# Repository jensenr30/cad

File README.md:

# Ryan's CAD Files (Schematics, PCBs, Simulations)

## kicad5
I started using KiCad 5.1.2 to draw schematics and lay out PCBs in May 2019.

## kicad4
I used KiCad 4.0.6 for 3 weeks in September 2017. The two projects I completed are:
* [Shift-Register Break-Out-Board](/kicad4/SRBOB) - A modular daisy-chain-able serial-in-parallel-out 74hc595-based shift register circuit board.
* [XPhone Input Board](/kicad4/XPhone/Input_Board) - A quad transducer amplifier and glockenspiel-key-hit-detection circuit board.

## eagle6
Eagle was the first CAD program I ever used. I started using Eagle (on version 5.11.0) sometime in early 2011. I stopped on version 6.6.0 in mid 2017.  Some of the more interesting projects I completed using Eagle are:
* [Analog Synth](eagle6/Analog%20Synth) - a bunch of analog (and digital) DIY synth modules.  Designed, built, and tested by your truly.  This includes VCOs, VCFs, VCAs, sequencers, front-panel designs, digital delay, manual oscillators, and power-distribution interconnect PCBs.
* [Stroboscope](eagle6/Stroboscope) - a device that can turn on and off LEDs very fast (at audio frequencies) in order to produce interesting/useful/helpful visual effects.  A stroboscope can be used to enable a human to monitor the rotation of things in real time, e.g. fans, drills, wheels, motors, spinning objects, guitar strings, and any other object engaged in cyclic motion.
* [VU Meter](eagle6/VU%20meter) - a circuit that represents audio amplitude vertically on several bargraphs (each bargraph displays the amplitude of a given section of the audio spectrum).  The device can be used to build a real-time visual audio spectrum analyzer.
* [FreqCount84](eagle6/FreqCount84) - Atmel microcontroller-based design for precise measurement of frequency of square waves.  I believe the hwardware & firmware achieved an accuracy of ± a few ppm with the help of a 1.5 pm TCXO.
* [9x9 LED Matrix](eagle6/9x9%20LED%20Matrix) - a 2D array of LEDs (9 LEDs wide, 9 LEDs tall).  I remember wanting to build an array that had an odd number of pixels because it would allow me to make symetric visual displays.  I programmed a game of pong for this 9x9 LED Matrix.  That code exists in [my repo for Arduino programs](https://github.com/jensenr30/Arduino/tree/master/_DISPLAY/9x9_LED_Matrix).
* [Prototype Boards](eagle6/Prototype%20Boards) - three PCBs that enable DIY circuit construction.  0.1"-arrays of SMD pads, 0.1"-arrays of through-holes, SOT-to-DIP break-out-boards, SOIC-to-DIP break-out-boards, etc...

## LTspice IV
I have used [LTspice](https://en.wikipedia.org/wiki/LTspice) version IV to simulate some of my circuits.

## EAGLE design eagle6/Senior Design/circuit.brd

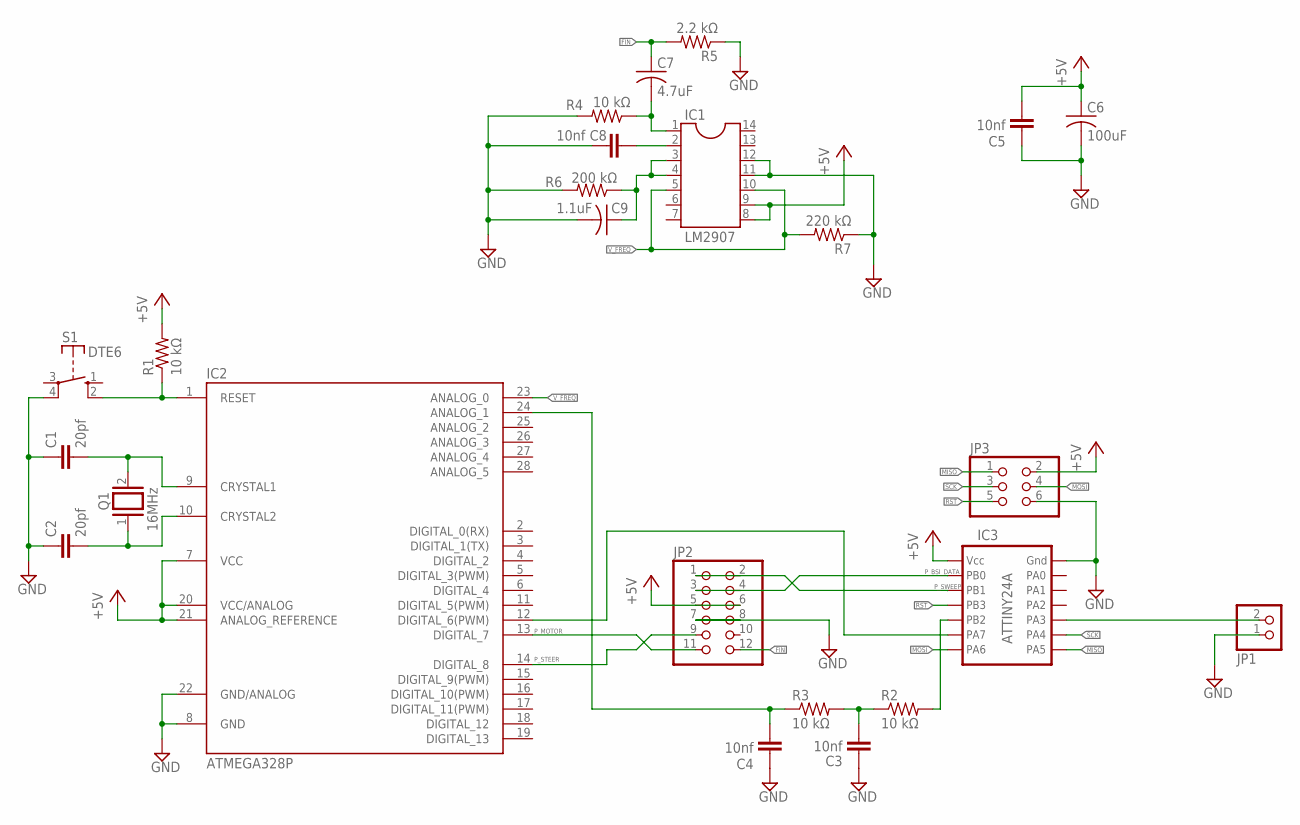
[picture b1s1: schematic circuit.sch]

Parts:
C1, C2: 20pf; C025-024X044
C3, C4, C5, C8: 10nf; C025-024X044
C6: 100uF; C025-050X050
C7: 4.7uF; C025-050X050
C9: 1.1uF; C025-050X050
IC1: LM2907; DIL14
IC2: ATMEGA328P; DIL28-3
IC3: ATTINY24A; TINY24A
JP1: PINHD-1X2; 1X02
JP2: PINHD-2X6; 2X06
JP3: PINHD-2X3; 2X03
Q1: 16MHz; QS
R1, R2, R3, R4: 10 kΩ; 0204V
R5: 2.2 kΩ; 0204V
R6: 200 kΩ; 0204V
R7: 220 kΩ; 0204V
S1: DTE6

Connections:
+5V: C5.2, C6.1, IC1.8, IC1.9, IC2.7 (VCC), IC2.20 (VCC/ANALOG), IC2.21 (ANALOG_REFERENCE), IC3.1, JP2.5, JP2.6, JP3.2, R1.2
DATA-READY: IC2.12 (DIGITAL_6(PWM)), IC3.6
FIN: C7.1, JP2.12, R5.2
GND: C1.1, C2.1, C3.1, C4.1, C5.1, C6.2, C8.1, C9.2, IC1.11, IC1.12, IC2.8 (GND), IC2.22 (GND/ANALOG), IC3.14, JP1.1, JP2.7, JP2.8, JP3.6, R4.2, R5.1, R6.2, R7.1, S1.4
LINE-POSITION: C4.2, IC2.24 (ANALOG_1), R3.1
MISO: IC3.8, JP3.1
MOSI: IC3.7, JP3.4
unnamed: C9.1, IC1.3, IC1.4, R6.1
unnamed: IC3.10, JP1.2
unnamed: IC3.5, R2.2
unnamed: C1.2, IC2.9 (CRYSTAL1), Q1.2
unnamed: C2.2, IC2.10 (CRYSTAL2), Q1.1
unnamed: C3.2, R2.1, R3.2
unnamed: IC2.1 (RESET), R1.1, S1.2 (S)
unnamed: C7.2, IC1.1, R4.1
unnamed: C8.2, IC1.2
P_BSI_DATA: IC3.2, JP2.3, JP2.4
P_MOTOR: IC2.13 (DIGITAL_7), JP2.11
P_STEER: IC2.14 (DIGITAL_8), JP2.9
P_SWEEP: IC3.3, JP2.1, JP2.2
RST: IC3.4, JP3.5
SCK: IC3.9, JP3.3
V_FREQ: IC1.5, IC1.10, IC2.23 (ANALOG_0), R7.2

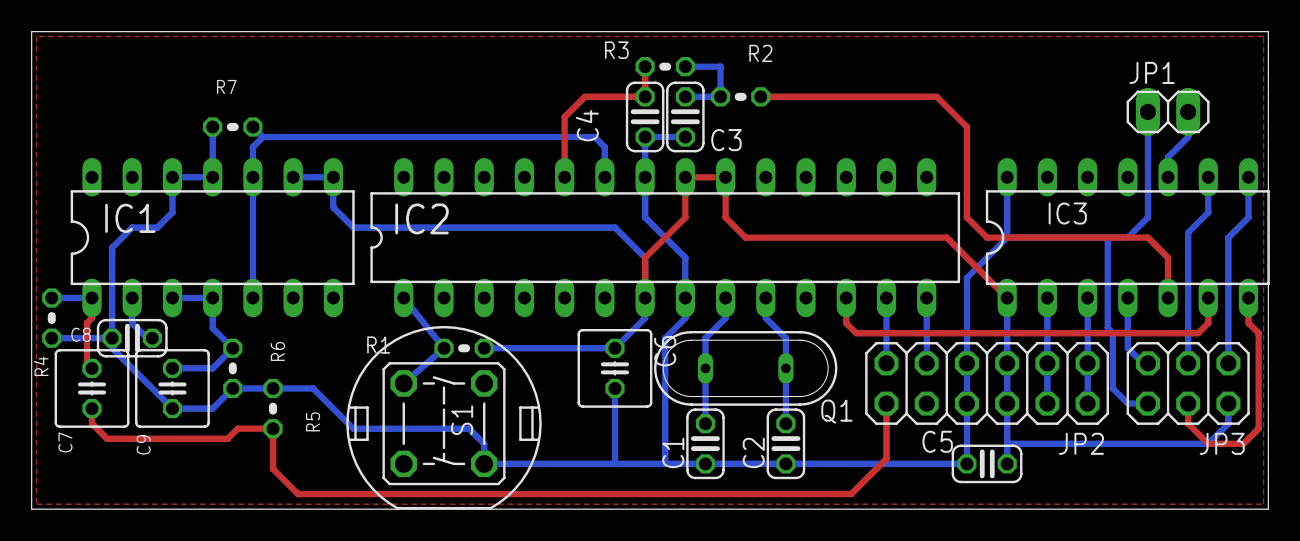
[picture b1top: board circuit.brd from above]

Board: 2 copper layers, 78.1 x 30.1 mm, 24 parts (0 on the bottom side), 23 nets.

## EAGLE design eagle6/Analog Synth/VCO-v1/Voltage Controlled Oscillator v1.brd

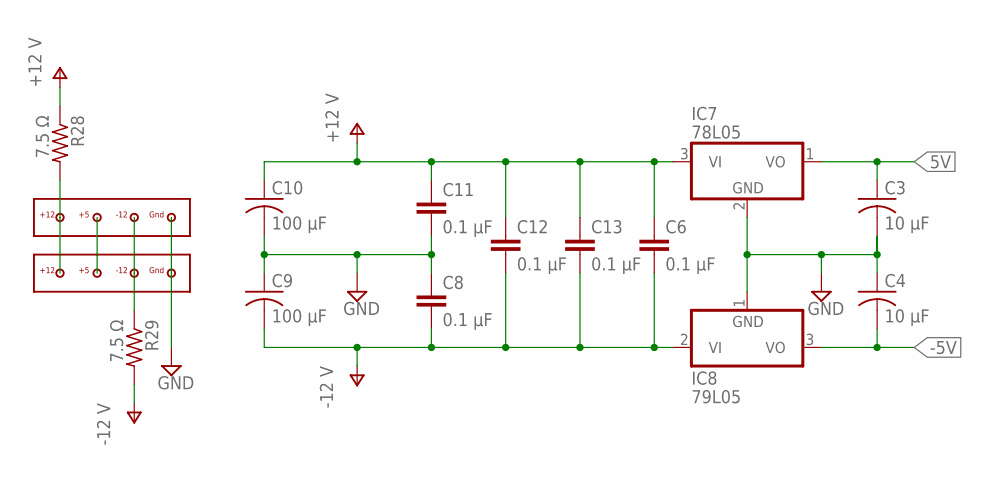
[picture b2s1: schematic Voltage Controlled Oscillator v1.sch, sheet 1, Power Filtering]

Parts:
C3, C4: 10 µF; C025-060X050
C6, C8, C11, C12, C13: 0.1 µF; C5B2.5
C9, C10: 100 µF; C025-060X050
IC7: 78L05; TO92
IC8: 79L05; TO92
R28, R29: 7.5 Ω; 0204/7
U$1, U$2: POWER_CONNECTOR_4_RGBB

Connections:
5V: C3.1, IC7.1 (VO); also elsewhere on the board
-5V: C4.2, IC8.3 (VO); also elsewhere on the board
GND: C3.2, C4.1, C8.1, C9.1, C10.2, C11.2, IC7.2 (GND), IC8.1 (GND), U$1.GND, U$2.GND; also elsewhere on the board
unnamed: U$1.+5, U$2.+5
unnamed: R28.2, U$1.+12, U$2.+12
unnamed: R29.1, U$1.-12, U$2.-12
V+: C6.1, C10.1, C11.1, C12.1, C13.1, IC7.3 (VI), R28.1; also elsewhere on the board
V-: C6.2, C8.2, C9.2, C12.2, C13.2, IC8.2 (VI), R29.2; also elsewhere on the board

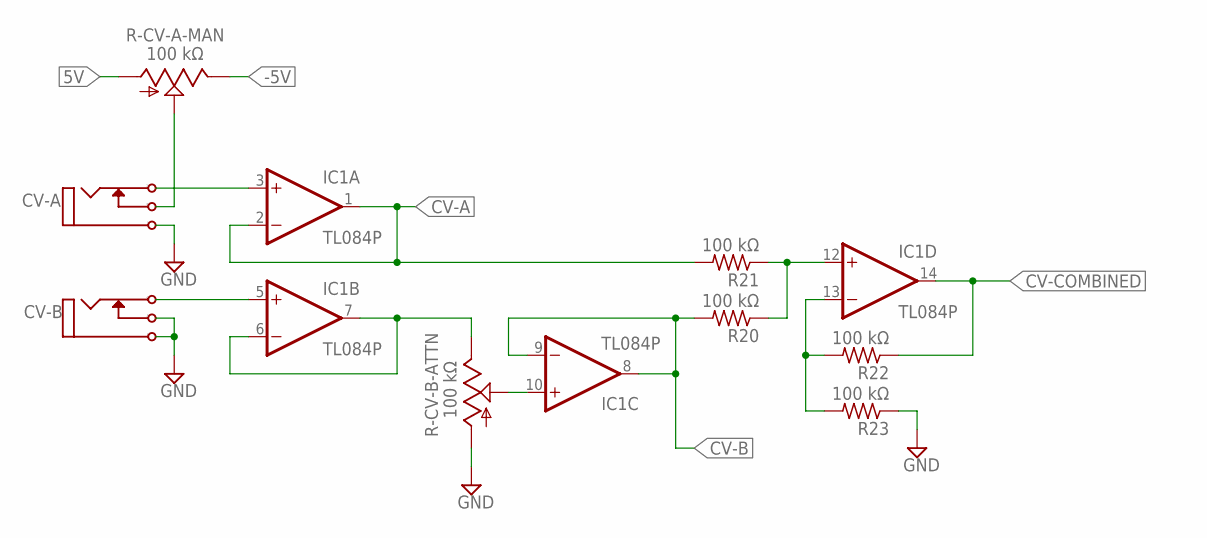
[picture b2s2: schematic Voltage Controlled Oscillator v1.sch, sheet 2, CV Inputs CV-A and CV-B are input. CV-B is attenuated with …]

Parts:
CV-A: I/O; MONO_JACK
CV-B: I/O; MONO_JACK
IC1: TL084P; DIL14
R20, R21, R22, R23: 100 kΩ; 0204/7
R-CV-A-MAN: 100 kΩ; B64Y
R-CV-B-ATTN: 100 kΩ; B64Y

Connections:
5V: R-CV-A-MAN.A; also elsewhere on the board
-5V: R-CV-A-MAN.E; also elsewhere on the board
CV-A: IC1.1 (OUT), IC1.2 (-IN), R21.2; also elsewhere on the board
CV-B: IC1.8 (OUT), IC1.9 (-IN), R20.2; also elsewhere on the board
CV-COMBINED: IC1.14 (OUT), R22.1; also elsewhere on the board
GND: CV-A.P$1, CV-B.P$1, CV-B.P$3 (P3), R23.1, R-CV-B-ATTN.A; also elsewhere on the board
unnamed: IC1.10 (+IN), R-CV-B-ATTN.S
unnamed: CV-A.P$2 (P2), IC1.3 (+IN)
unnamed: CV-A.P$3 (P3), R-CV-A-MAN.S
unnamed: IC1.12 (+IN), R20.1, R21.1
unnamed: IC1.13 (-IN), R22.2, R23.2
unnamed: CV-B.P$2 (P2), IC1.5 (+IN)
unnamed: IC1.6 (-IN), IC1.7 (OUT), R-CV-B-ATTN.E
V+: IC1.4 (V+); also elsewhere on the board
V-: IC1.11 (V-); also elsewhere on the board

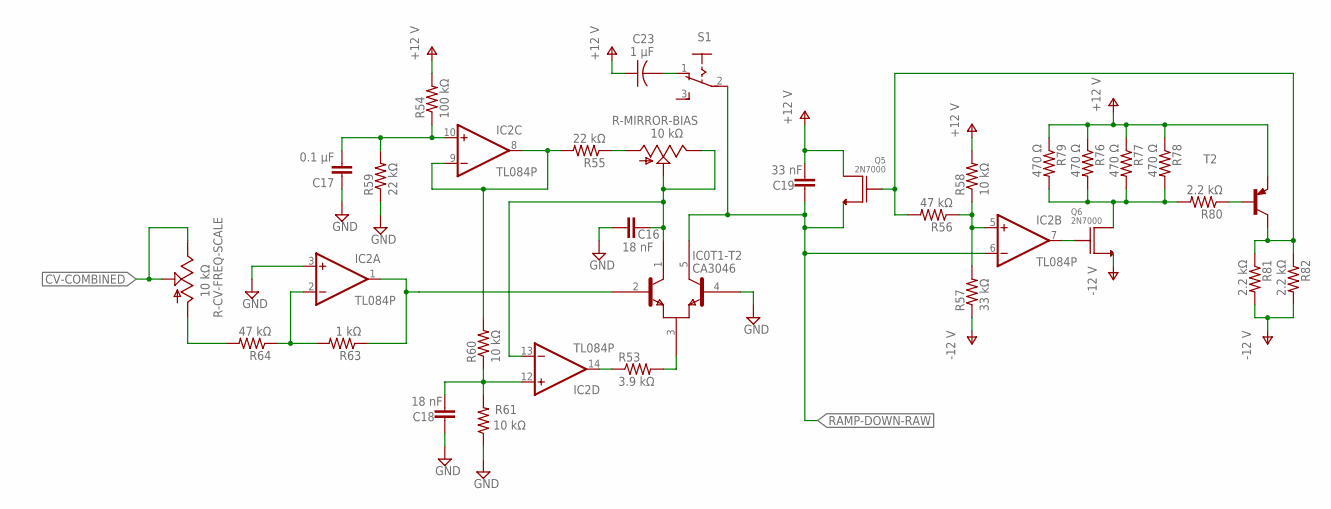
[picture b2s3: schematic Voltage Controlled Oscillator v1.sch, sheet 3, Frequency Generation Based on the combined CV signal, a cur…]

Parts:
C16, C18: 18 nF; C2.5-2
C17: 0.1 µF; C5B2.5
C19: 33 nF; C2.5-2
C23: 1 µF; C025-060X050
IC0: CA3046; DIL14
IC2: TL084P; DIL14
Q5, Q6: 2N7000
R53: 3.9 kΩ; 0204/7
R54: 100 kΩ; 0204/7
R55, R59: 22 kΩ; 0204/7
R56, R64: 47 kΩ; 0204/7
R57: 33 kΩ; 0204/7
R58, R60, R61: 10 kΩ; 0204/7
R63: 1 kΩ; 0204/7
R76, R77, R78, R79: 470 Ω; 0204/7
R80, R81, R82: 2.2 kΩ; 0204/7
R-CV-FREQ-SCALE: 10 kΩ; B64Y
R-MIRROR-BIAS: 10 kΩ; B64Y
S1: 255SB
T2: 2N3906-PNP-TO92-EBC; TO92-EBC

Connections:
CV-COMBINED: R-CV-FREQ-SCALE.E, R-CV-FREQ-SCALE.S; also elsewhere on the board
GND: C16.2, C17.1, C18.1, IC0.4 (B2), IC2.3 (+IN), R59.1, R61.1; also elsewhere on the board
unnamed: IC0.3 (E), R53.2
unnamed: IC2.14 (OUT), R53.1
unnamed: C17.2, IC2.10 (+IN), R54.1, R59.2
unnamed: IC2.9 (-IN), R60.2
unnamed: IC2.8 (OUT), R55.2
unnamed: R55.1, R-MIRROR-BIAS.A
unnamed: C16.1, IC0.1 (C1), IC2.13 (-IN), R-MIRROR-BIAS.E, R-MIRROR-BIAS.S
unnamed: C18.2, IC2.12 (+IN), R60.1, R61.2
unnamed: IC2.5 (+IN), R56.1, R57.2, R58.1
unnamed: IC2.1 (OUT), R63.1
unnamed: IC2.2 (-IN), R63.2, R64.1
unnamed: R64.2, R-CV-FREQ-SCALE.A
unnamed: IC2.7 (OUT), Q6.G
unnamed: Q6.D, R76.2, R77.2, R78.2, R79.2, R80.2
unnamed: R80.1, T2.B
unnamed: Q5.G, R56.2, R81.1, R82.1, T2.C
unnamed: C23.2, S1.1 (O)
RAMP-DOWN-RAW: C19.1, IC0.5 (C2), IC2.6 (-IN), Q5.S, S1.2; also elsewhere on the board
V+: C19.2, C23.1, IC2.4 (V+), Q5.D, R54.2, R58.2, R76.1, R77.1, R78.1, R79.1, T2.E; also elsewhere on the board
V-: IC2.11 (V-), Q6.S, R57.1, R81.2, R82.2; also elsewhere on the board

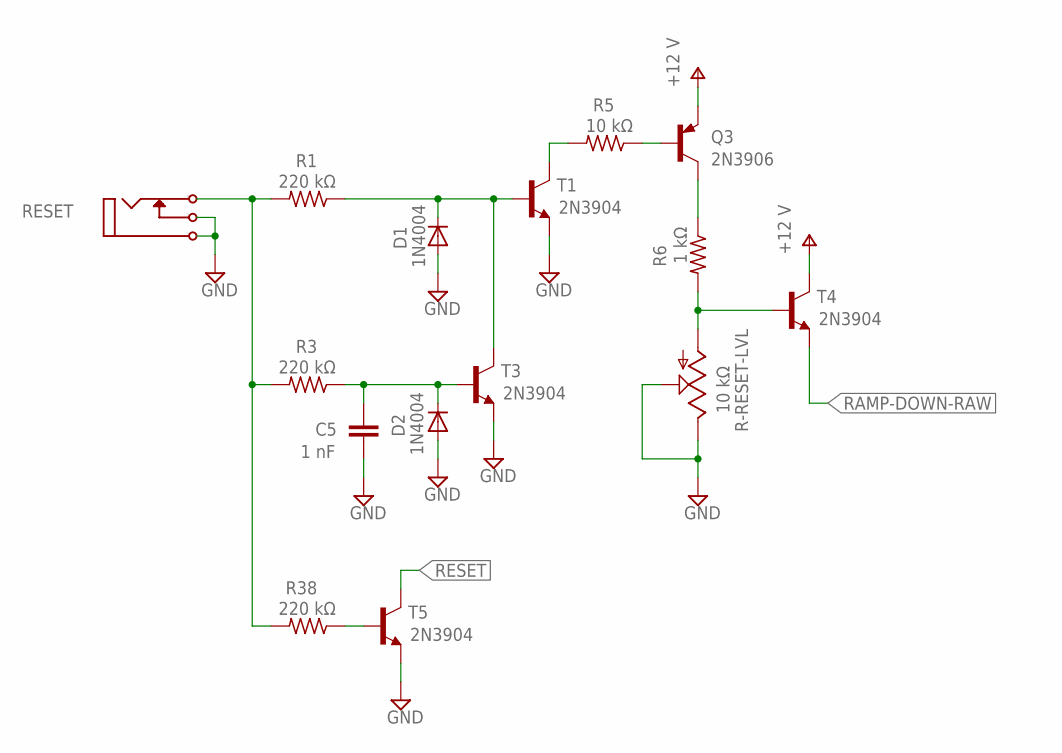
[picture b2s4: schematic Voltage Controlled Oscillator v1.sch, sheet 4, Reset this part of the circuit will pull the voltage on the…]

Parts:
C5: 1 nF; C2.5-2
D1, D2: 1N4004; DO41-10
Q3: 2N3906; TO92
R1, R3, R38: 220 kΩ; 0204/7
R5: 10 kΩ; 0204/7
R6: 1 kΩ; 0204/7
R-RESET-LVL: 10 kΩ; B64Y
RESET: I/O; MONO_JACK
T1, T3, T4, T5: 2N3904; TO92

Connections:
47393747: Q3.1 (C), R6.1
GND: C5.1, D1.A, D2.A, R-RESET-LVL.E, R-RESET-LVL.S, RESET.P$1, RESET.P$3 (P3), T1.3 (E), T3.3 (E), T5.3 (E); also elsewhere on the board
unnamed: R38.1, T5.2 (B)
unnamed: C5.2, D2.C, R3.1, T3.2 (B)
unnamed: R5.2, T1.1 (C)
unnamed: R1.2, R3.2, R38.2, RESET.P$2 (P2)
unnamed: D1.C, R1.1, T1.2 (B), T3.1 (C)
unnamed: Q3.2 (B), R5.1
unnamed: R6.2, R-RESET-LVL.A, T4.2 (B)
RAMP-DOWN-RAW: T4.3 (E); also elsewhere on the board
RESET: T5.1 (C); also elsewhere on the board
V+: Q3.3 (E), T4.1 (C); also elsewhere on the board

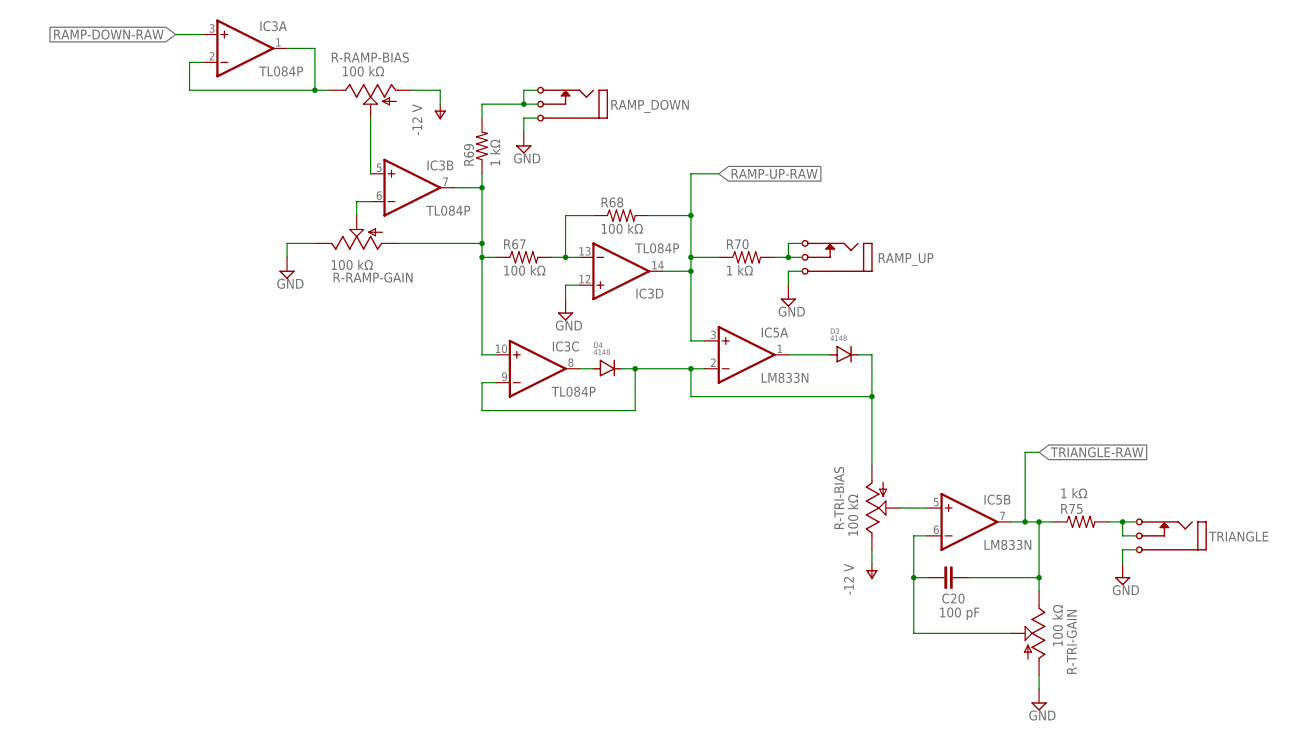
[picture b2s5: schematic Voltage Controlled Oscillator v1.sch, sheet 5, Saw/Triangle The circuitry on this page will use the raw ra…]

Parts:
C20: 100 pF; C2.5-2
D3, D4: 4148; DIODE-0204/5
IC3: TL084P; DIL14
IC5: LM833N; DIL08
R67, R68: 100 kΩ; 0204/7
R69, R70, R75: 1 kΩ; 0204/7
R-RAMP-BIAS: 100 kΩ; B64Y
R-RAMP-GAIN: 100 kΩ; B64Y
R-TRI-BIAS: 100 kΩ; B64Y
R-TRI-GAIN: 100 kΩ; B64Y
RAMP_DOWN: I/O; MONO_JACK
RAMP_UP: I/O; MONO_JACK
TRIANGLE: I/O; MONO_JACK

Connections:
ASASDFASDF: IC3.7 (OUT), IC3.10 (+IN), R67.1, R69.1, R-RAMP-GAIN.A
GND: IC3.12 (+IN), R-RAMP-GAIN.E, R-TRI-GAIN.A, RAMP_DOWN.P$1, RAMP_UP.P$1, TRIANGLE.P$1; also elsewhere on the board
unnamed: IC5.5 (+IN), R-TRI-BIAS.S
unnamed: IC3.1 (OUT), IC3.2 (-IN), R-RAMP-BIAS.E
unnamed: IC3.6 (-IN), R-RAMP-GAIN.S
unnamed: IC3.13 (-IN), R67.2, R68.1
unnamed: D4.ANODE, IC3.8 (OUT)
unnamed: D3.ANODE, IC5.1 (OUT)
unnamed: D3.CATHODE, D4.CATHODE, IC3.9 (-IN), IC5.2 (-IN), R-TRI-BIAS.A
unnamed: C20.2, IC5.6 (-IN), R-TRI-GAIN.S
unnamed: R75.2, TRIANGLE.P$2 (P2), TRIANGLE.P$3 (P3)
unnamed: IC3.5 (+IN), R-RAMP-BIAS.S
RAMP-DOWN-RAW: IC3.3 (+IN); also elsewhere on the board
RAMP-UP-RAW: IC3.14 (OUT), IC5.3 (+IN), R68.2, R70.1; also elsewhere on the board
RAMP_DOWN1: R69.2, RAMP_DOWN.P$2 (P2), RAMP_DOWN.P$3 (P3)
RAMP_UP2: R70.2, RAMP_UP.P$2 (P2), RAMP_UP.P$3 (P3)
TRIANGLE-RAW: C20.1, IC5.7 (OUT), R75.1, R-TRI-GAIN.E; also elsewhere on the board
V+: IC3.4 (V+), IC5.8 (V+); also elsewhere on the board
V-: IC3.11 (V-), IC5.4 (V-), R-RAMP-BIAS.A, R-TRI-BIAS.E; also elsewhere on the board

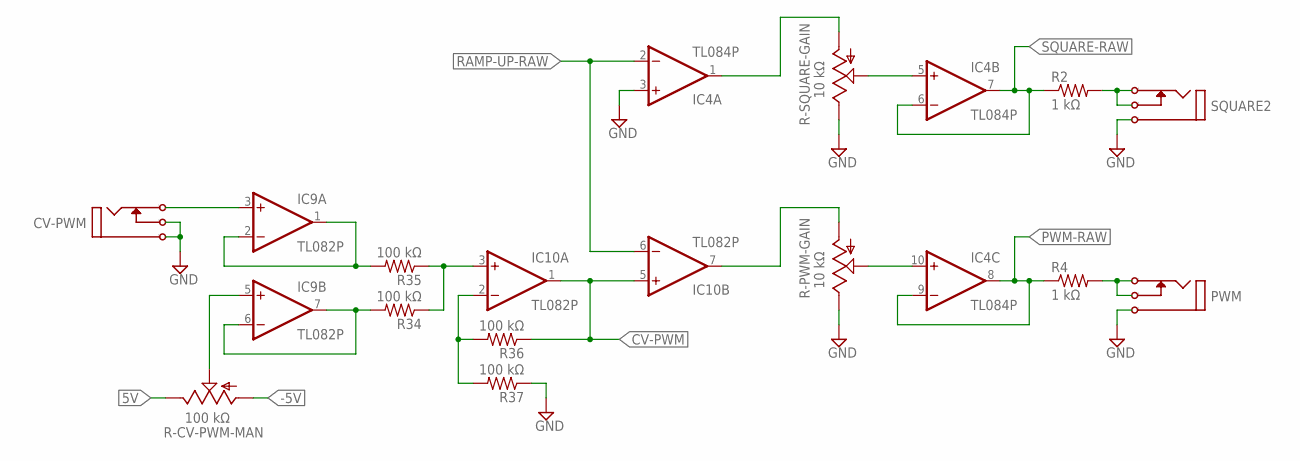
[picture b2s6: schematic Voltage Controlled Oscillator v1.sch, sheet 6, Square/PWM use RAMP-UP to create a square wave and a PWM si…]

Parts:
CV-PWM: I/O; MONO_JACK
IC4: TL084P; DIL14
IC9, IC10: TL082P; DIL08
PWM: I/O; MONO_JACK
R2, R4: 1 kΩ; 0204/7
R34, R35, R36, R37: 100 kΩ; 0204/7
R-CV-PWM-MAN: 100 kΩ; B64Y
R-PWM-GAIN: 10 kΩ; B64Y
R-SQUARE-GAIN: 10 kΩ; B64Y
SQUARE2: I/O; MONO_JACK

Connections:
5V: R-CV-PWM-MAN.E; also elsewhere on the board
83NF8Q8FJA: IC9.1 (OUT), IC9.2 (-IN), R35.2
-5V: R-CV-PWM-MAN.A; also elsewhere on the board
CV-B: IC9.6 (-IN), IC9.7 (OUT), R34.2; also elsewhere on the board
CV-PWM: IC10.1 (OUT), IC10.5 (+IN), R36.1; also elsewhere on the board
GND: CV-PWM.P$1, CV-PWM.P$3 (P3), IC4.3 (+IN), PWM.P$1, R37.1, R-PWM-GAIN.E, R-SQUARE-GAIN.E, SQUARE2.P$1; also elsewhere on the board
unnamed: IC4.5 (+IN), R-SQUARE-GAIN.S
unnamed: IC4.1 (OUT), R-SQUARE-GAIN.A
unnamed: R2.2, SQUARE2.P$2 (P2), SQUARE2.P$3 (P3)
unnamed: IC4.10 (+IN), R-PWM-GAIN.S
unnamed: IC10.7 (OUT), R-PWM-GAIN.A
unnamed: PWM.P$2 (P2), PWM.P$3 (P3), R4.2
unnamed: CV-PWM.P$2 (P2), IC9.3 (+IN)
unnamed: IC10.3 (+IN), R34.1, R35.1
unnamed: IC10.2 (-IN), R36.2, R37.2
PWM-RAW: IC4.8 (OUT), IC4.9 (-IN), R4.1; also elsewhere on the board
RAMP-UP-RAW: IC4.2 (-IN), IC10.6 (-IN); also elsewhere on the board
SQUARE-RAW: IC4.6 (-IN), IC4.7 (OUT), R2.1; also elsewhere on the board
V+: IC4.4 (V+), IC9.8 (V+), IC10.8 (V+); also elsewhere on the board
V-: IC4.11 (V-), IC9.4 (V-), IC10.4 (V-); also elsewhere on the board

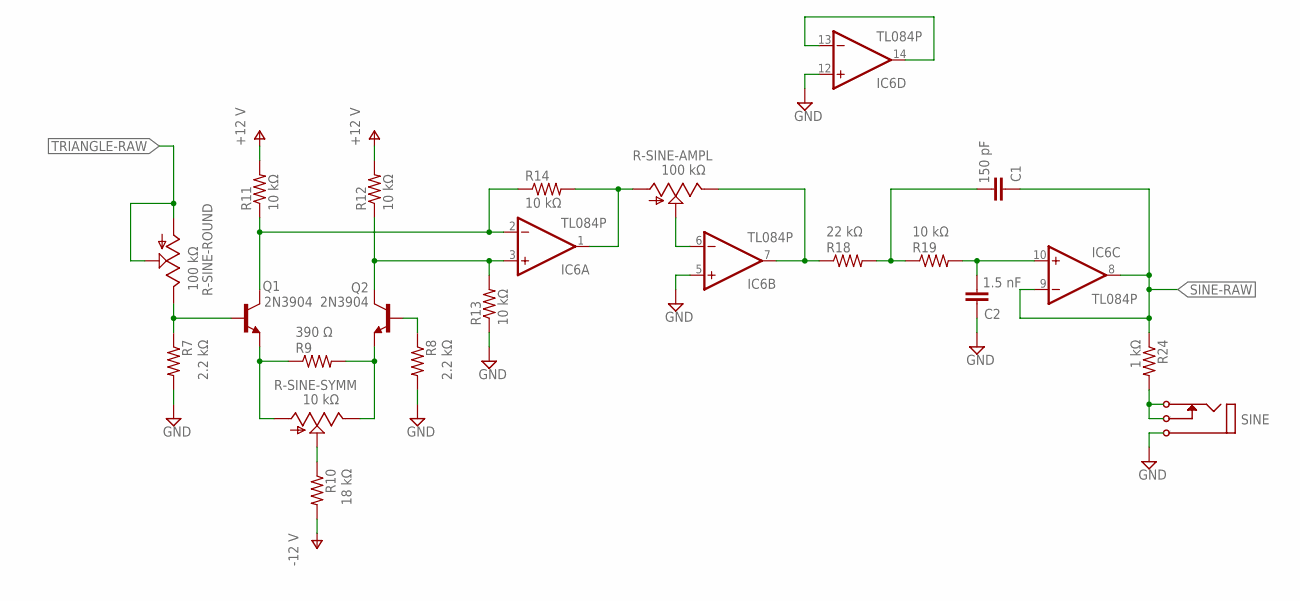
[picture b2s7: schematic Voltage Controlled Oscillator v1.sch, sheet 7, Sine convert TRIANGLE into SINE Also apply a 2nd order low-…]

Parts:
C1: 150 pF; C2.5-2
C2: 1.5 nF; C2.5-2
IC6: TL084P; DIL14
Q1, Q2: 2N3904; TO92
R7, R8: 2.2 kΩ; 0204/7
R9: 390 Ω; 0204/7
R10: 18 kΩ; 0204/7
R11, R12, R13, R14, R19: 10 kΩ; 0204/7
R18: 22 kΩ; 0204/7
R24: 1 kΩ; 0204/7
R-SINE-AMPL: 100 kΩ; B64Y
R-SINE-ROUND: 100 kΩ; B64Y
R-SINE-SYMM: 10 kΩ; B64Y
SINE: I/O; MONO_JACK

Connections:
GND: C2.1, IC6.5 (+IN), IC6.12 (+IN), R7.2, R8.2, R13.1, SINE.P$1; also elsewhere on the board
unnamed: IC6.6 (-IN), R-SINE-AMPL.S
unnamed: Q1.2 (B), R7.1, R-SINE-ROUND.E
unnamed: Q2.2 (B), R8.1
unnamed: Q1.3 (E), R9.1, R-SINE-SYMM.A
unnamed: Q2.3 (E), R9.2, R-SINE-SYMM.E
unnamed: R10.1, R-SINE-SYMM.S
unnamed: IC6.2 (-IN), Q1.1 (C), R11.1, R14.1
unnamed: IC6.1 (OUT), R14.2, R-SINE-AMPL.A
unnamed: IC6.3 (+IN), Q2.1 (C), R12.1, R13.2
unnamed: IC6.7 (OUT), R18.1, R-SINE-AMPL.E
unnamed: C1.2, R18.2, R19.1
unnamed: C2.2, IC6.10 (+IN), R19.2
unnamed: IC6.13 (-IN), IC6.14 (OUT)
RAMP_UP1: R24.2, SINE.P$2 (P2), SINE.P$3 (P3)
SINE-RAW: C1.1, IC6.8 (OUT), IC6.9 (-IN), R24.1; also elsewhere on the board
TRIANGLE-RAW: R-SINE-ROUND.A, R-SINE-ROUND.S; also elsewhere on the board
V+: IC6.4 (V+), R11.2, R12.2; also elsewhere on the board
V-: IC6.11 (V-), R10.2; also elsewhere on the board

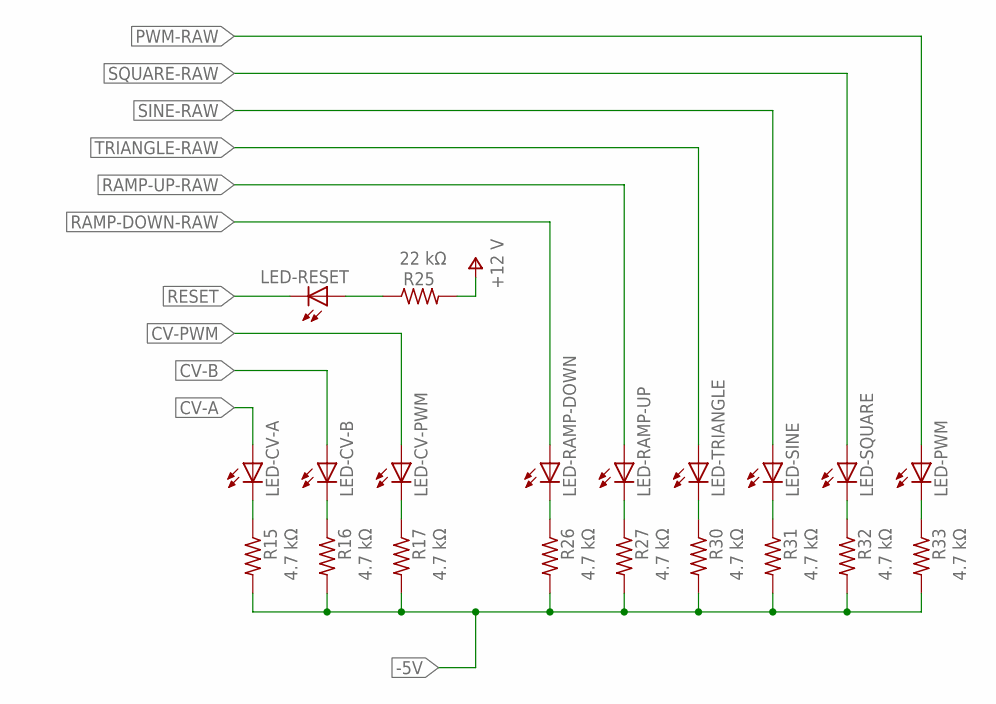
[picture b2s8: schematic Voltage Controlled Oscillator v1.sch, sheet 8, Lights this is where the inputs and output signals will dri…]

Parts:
LED-CV-A: LED3MM
LED-CV-B: LED3MM
LED-CV-PWM: LED3MM
LED-PWM: LED3MM
LED-RAMP-DOWN: LED3MM
LED-RAMP-UP: LED3MM
LED-RESET: LED3MM
LED-SINE: LED3MM
LED-SQUARE: LED3MM
LED-TRIANGLE: LED3MM
R15, R16, R17, R26, R27, R30, R31, R32, R33: 4.7 kΩ; 0204/7
R25: 22 kΩ; 0204/7

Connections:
-5V: R15.2, R16.2, R17.2, R26.2, R27.2, R30.2, R31.2, R32.2, R33.2; also elsewhere on the board
CV-A: LED-CV-A.A; also elsewhere on the board
CV-B: LED-CV-B.A; also elsewhere on the board
CV-PWM: LED-CV-PWM.A; also elsewhere on the board
unnamed: LED-RESET.A, R25.1
unnamed: LED-CV-A.K (C), R15.1
unnamed: LED-CV-B.K (C), R16.1
unnamed: LED-CV-PWM.K (C), R17.1
unnamed: LED-RAMP-DOWN.K (C), R26.1
unnamed: LED-RAMP-UP.K (C), R27.1
unnamed: LED-TRIANGLE.K (C), R30.1
unnamed: LED-SINE.K (C), R31.1
unnamed: LED-SQUARE.K (C), R32.1
unnamed: LED-PWM.K (C), R33.1
PWM-RAW: LED-PWM.A; also elsewhere on the board
RAMP-DOWN-RAW: LED-RAMP-DOWN.A; also elsewhere on the board
RAMP-UP-RAW: LED-RAMP-UP.A; also elsewhere on the board
RESET: LED-RESET.K (C); also elsewhere on the board
SINE-RAW: LED-SINE.A; also elsewhere on the board
SQUARE-RAW: LED-SQUARE.A; also elsewhere on the board
TRIANGLE-RAW: LED-TRIANGLE.A; also elsewhere on the board
V+: R25.2; also elsewhere on the board

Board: 2 copper layers, 142 parts (0 on the bottom side), 98 nets, no tracks yet.

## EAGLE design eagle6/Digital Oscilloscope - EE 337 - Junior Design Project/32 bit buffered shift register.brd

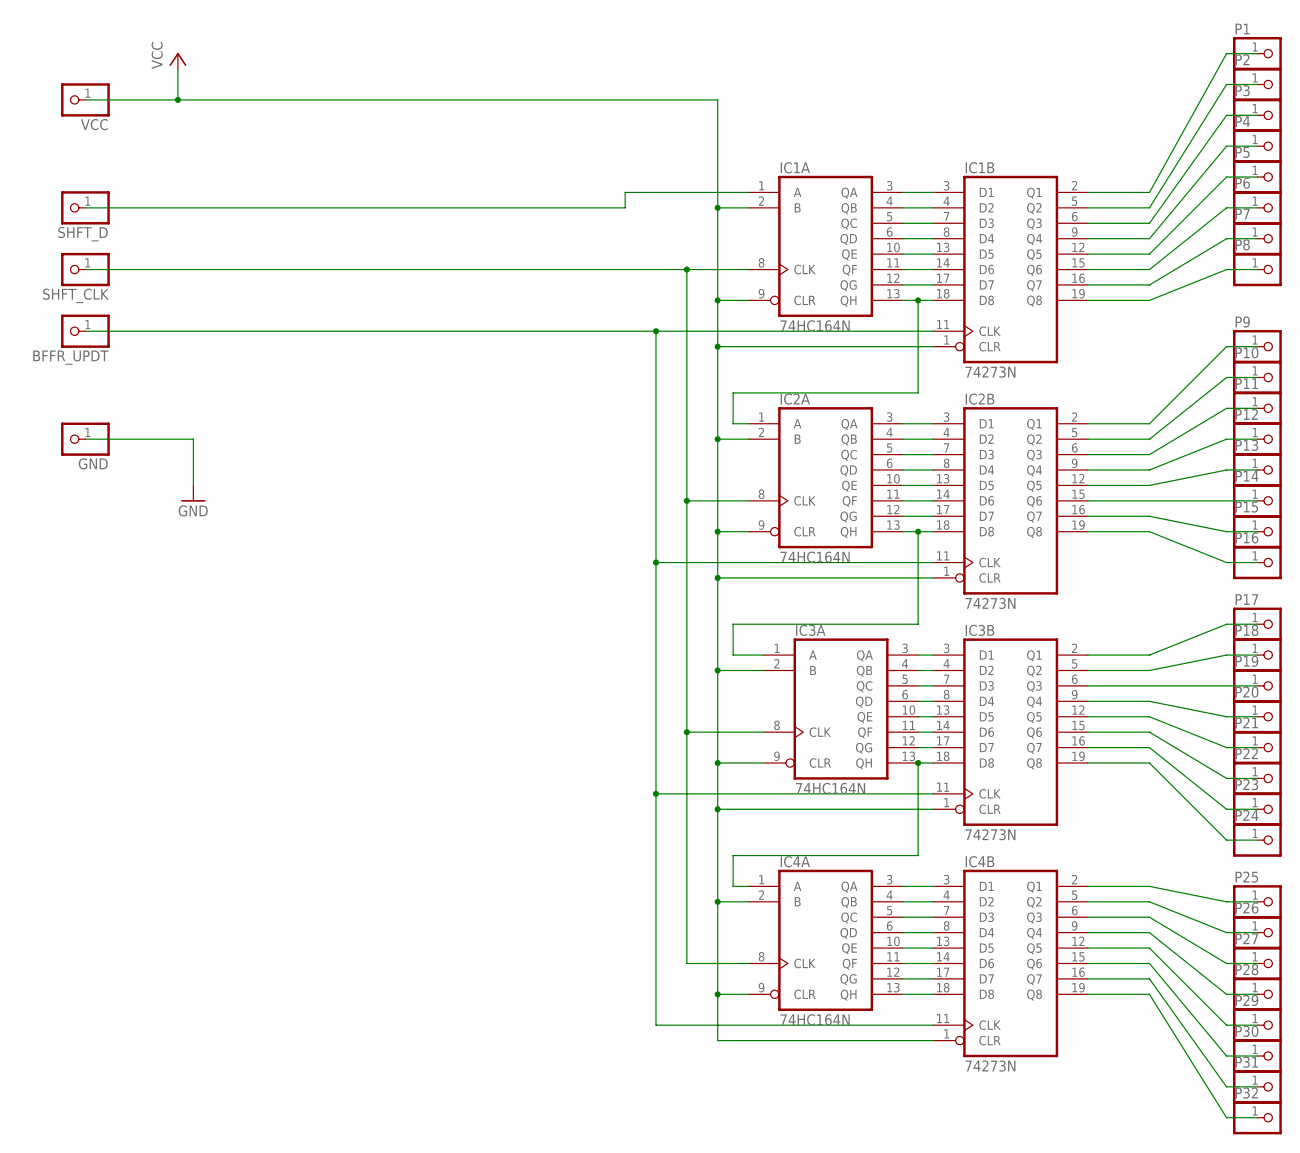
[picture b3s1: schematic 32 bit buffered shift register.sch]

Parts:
BFFR_UPDT: PINHD-1X1; 1X01
GND: PINHD-1X1; 1X01
IC1A, IC2A, IC3A, IC4A: 74HC164N; DIL14
IC1B, IC2B, IC3B, IC4B: 74273N; DIL20
P1, P2, P3, P4, P5, P6, P7, P8, P9, P10, P11, P12, P13, P14, P15, P16, P17, P18, P19, P20, P21, P22, P23, P24, P25, P26, P27, P28, P29, P30, P31, P32: PINHD-1X1; 1X01
SHFT_CLK: PINHD-1X1; 1X01
SHFT_D: PINHD-1X1; 1X01
VCC: PINHD-1X1; 1X01

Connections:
GND: GND.1, IC1A.7 (GND), IC1B.10 (GND), IC2A.7 (GND), IC2B.10 (GND), IC3A.7 (GND), IC3B.10 (GND), IC4A.7 (GND), IC4B.10 (GND)
unnamed: IC1B.2 (Q1), P1.1
unnamed: IC1B.5 (Q2), P2.1
unnamed: IC1B.6 (Q3), P3.1
unnamed: IC1B.9 (Q4), P4.1
unnamed: IC1B.12 (Q5), P5.1
unnamed: IC1B.15 (Q6), P6.1
unnamed: IC1B.16 (Q7), P7.1
unnamed: IC1B.19 (Q8), P8.1
unnamed: IC2B.2 (Q1), P9.1
unnamed: IC2B.5 (Q2), P10.1
unnamed: IC2B.6 (Q3), P11.1
unnamed: IC2B.9 (Q4), P12.1
unnamed: IC2B.12 (Q5), P13.1
unnamed: IC2B.15 (Q6), P14.1
unnamed: IC2B.16 (Q7), P15.1
unnamed: IC2B.19 (Q8), P16.1
unnamed: IC3B.2 (Q1), P17.1
unnamed: IC3B.5 (Q2), P18.1
unnamed: IC3B.6 (Q3), P19.1
unnamed: IC3B.9 (Q4), P20.1
unnamed: IC3B.12 (Q5), P21.1
unnamed: IC3B.15 (Q6), P22.1
unnamed: IC3B.16 (Q7), P23.1
unnamed: IC3B.19 (Q8), P24.1
unnamed: IC4B.2 (Q1), P25.1
unnamed: IC4B.5 (Q2), P26.1
unnamed: IC4B.6 (Q3), P27.1
unnamed: IC4B.9 (Q4), P28.1
unnamed: IC4B.12 (Q5), P29.1
unnamed: IC4B.15 (Q6), P30.1
unnamed: IC4B.16 (Q7), P31.1
unnamed: IC4B.19 (Q8), P32.1
unnamed: IC1A.3 (QA), IC1B.3 (D1)
unnamed: IC1A.4 (QB), IC1B.4 (D2)
unnamed: IC1A.5 (QC), IC1B.7 (D3)
unnamed: IC1A.6 (QD), IC1B.8 (D4)
unnamed: IC1A.10 (QE), IC1B.13 (D5)
unnamed: IC1A.11 (QF), IC1B.14 (D6)
unnamed: IC1A.12 (QG), IC1B.17 (D7)
unnamed: IC1A.13 (QH), IC1B.18 (D8), IC2A.1 (A)
unnamed: IC2A.3 (QA), IC2B.3 (D1)
unnamed: IC2A.4 (QB), IC2B.4 (D2)
unnamed: IC2A.5 (QC), IC2B.7 (D3)
unnamed: IC2A.6 (QD), IC2B.8 (D4)
unnamed: IC2A.10 (QE), IC2B.13 (D5)
unnamed: IC2A.11 (QF), IC2B.14 (D6)
unnamed: IC2A.13 (QH), IC2B.18 (D8), IC3A.1 (A)
unnamed: IC3A.3 (QA), IC3B.3 (D1)
unnamed: IC3A.4 (QB), IC3B.4 (D2)
unnamed: IC3A.5 (QC), IC3B.7 (D3)
unnamed: IC3A.6 (QD), IC3B.8 (D4)
unnamed: IC3A.10 (QE), IC3B.13 (D5)
unnamed: IC3A.11 (QF), IC3B.14 (D6)
unnamed: IC3A.12 (QG), IC3B.17 (D7)
unnamed: IC3A.13 (QH), IC3B.18 (D8), IC4A.1 (A)
unnamed: IC4A.3 (QA), IC4B.3 (D1)
unnamed: IC4A.4 (QB), IC4B.4 (D2)
unnamed: IC4A.5 (QC), IC4B.7 (D3)
unnamed: IC4A.6 (QD), IC4B.8 (D4)
unnamed: IC4A.10 (QE), IC4B.13 (D5)
unnamed: IC4A.11 (QF), IC4B.14 (D6)
unnamed: IC4A.12 (QG), IC4B.17 (D7)
unnamed: IC4A.13 (QH), IC4B.18 (D8)
unnamed: BFFR_UPDT.1, IC1B.11 (CLK), IC2B.11 (CLK), IC3B.11 (CLK), IC4B.11 (CLK)
unnamed: IC1A.1 (A), SHFT_D.1
unnamed: IC1A.8 (CLK), IC2A.8 (CLK), IC3A.8 (CLK), IC4A.8 (CLK), SHFT_CLK.1
unnamed: IC2A.12 (QG), IC2B.17 (D7)
VCC: IC1A.2 (B), IC1A.9 (CLR), IC1A.14 (VCC), IC1B.1 (CLR), IC1B.20 (VCC), IC2A.2 (B), IC2A.9 (CLR), IC2A.14 (VCC), IC2B.1 (CLR), IC2B.20 (VCC), IC3A.2 (B), IC3A.9 (CLR), IC3A.14 (VCC), IC3B.1 (CLR), IC3B.20 (VCC), IC4A.2 (B), IC4A.9 (CLR), IC4A.14 (VCC), IC4B.1 (CLR), IC4B.20 (VCC), VCC.1

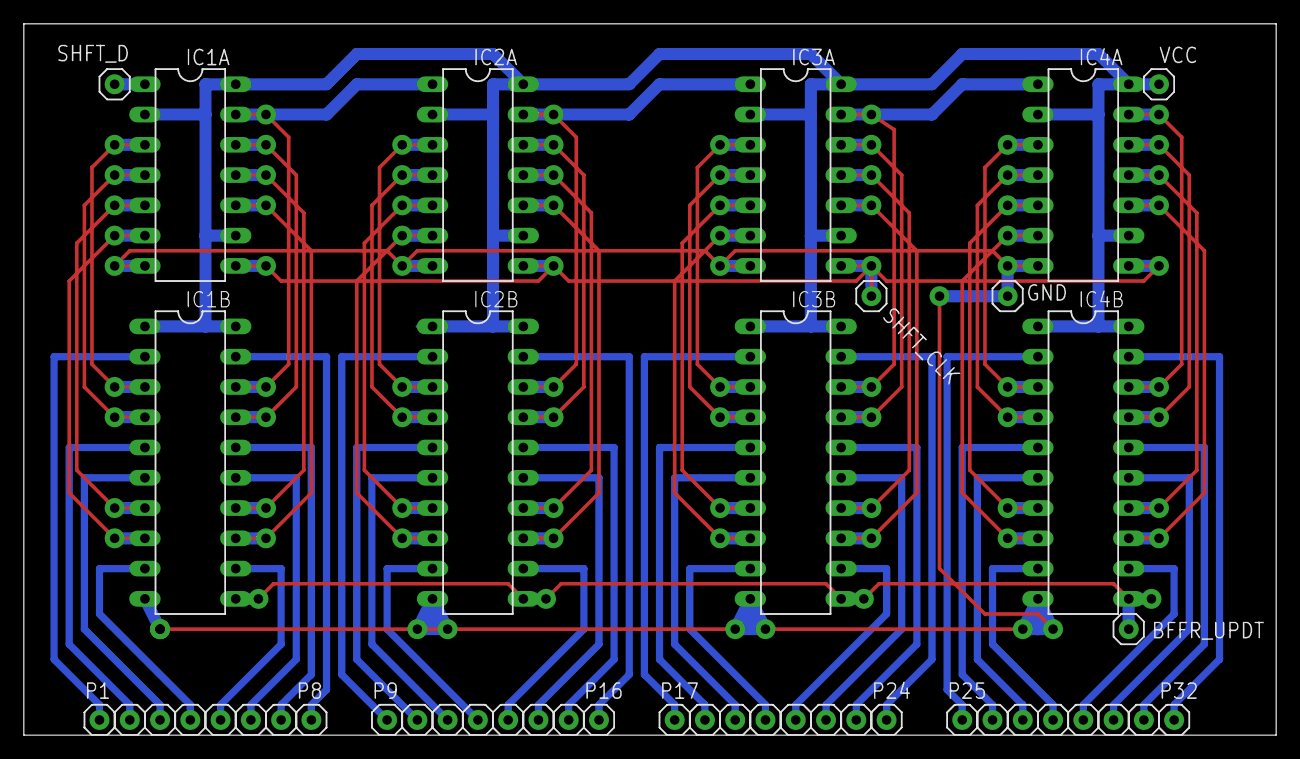
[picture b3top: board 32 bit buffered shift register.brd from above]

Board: 2 copper layers, 105.1 x 59.7 mm, 45 parts (0 on the bottom side), 69 nets.

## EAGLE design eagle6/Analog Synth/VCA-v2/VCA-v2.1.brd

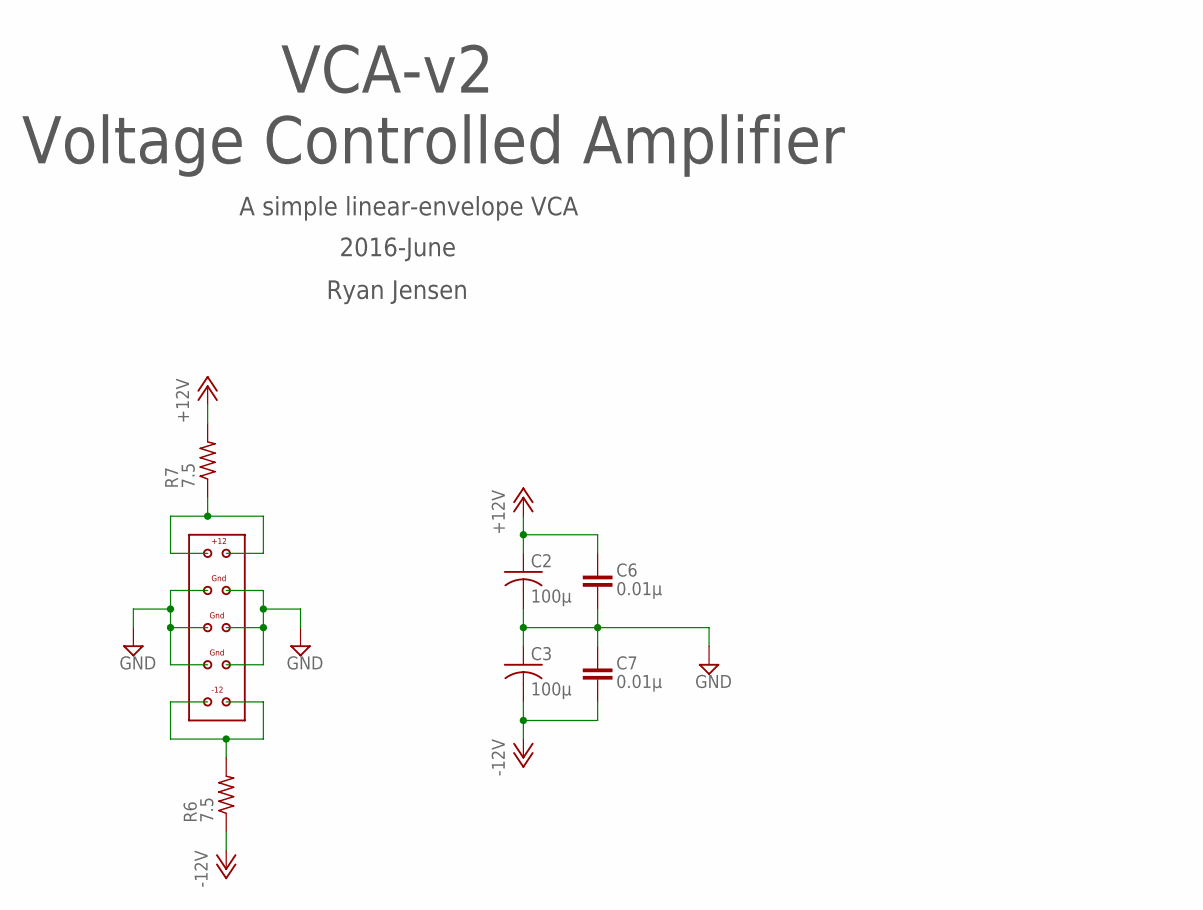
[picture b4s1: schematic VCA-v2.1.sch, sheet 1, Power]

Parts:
C2, C3: 100µ; C025-050X050
C6, C7: 0.01µ; C0603
R6, R7: 7.5; R0603
U$1: EURORACK-POWER

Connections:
+12V: C2.1, C6.1, R7.2; also elsewhere on the board
-12V: C3.2, C7.2, R6.1; also elsewhere on the board
GND: C2.2, C3.1, C6.2, C7.1, U$1.P$3, U$1.P$4, U$1.P$5, U$1.P$6, U$1.P$7, U$1.P$8; also elsewhere on the board
unnamed: R6.2, U$1.P$9, U$1.P$10
unnamed: R7.1, U$1.P$1, U$1.P$2

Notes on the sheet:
VCA-v2 Voltage Controlled Amplifier
A simple linear-envelope VCA
Ryan Jensen
2016-June

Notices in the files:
parts and their libraries:
CC0
